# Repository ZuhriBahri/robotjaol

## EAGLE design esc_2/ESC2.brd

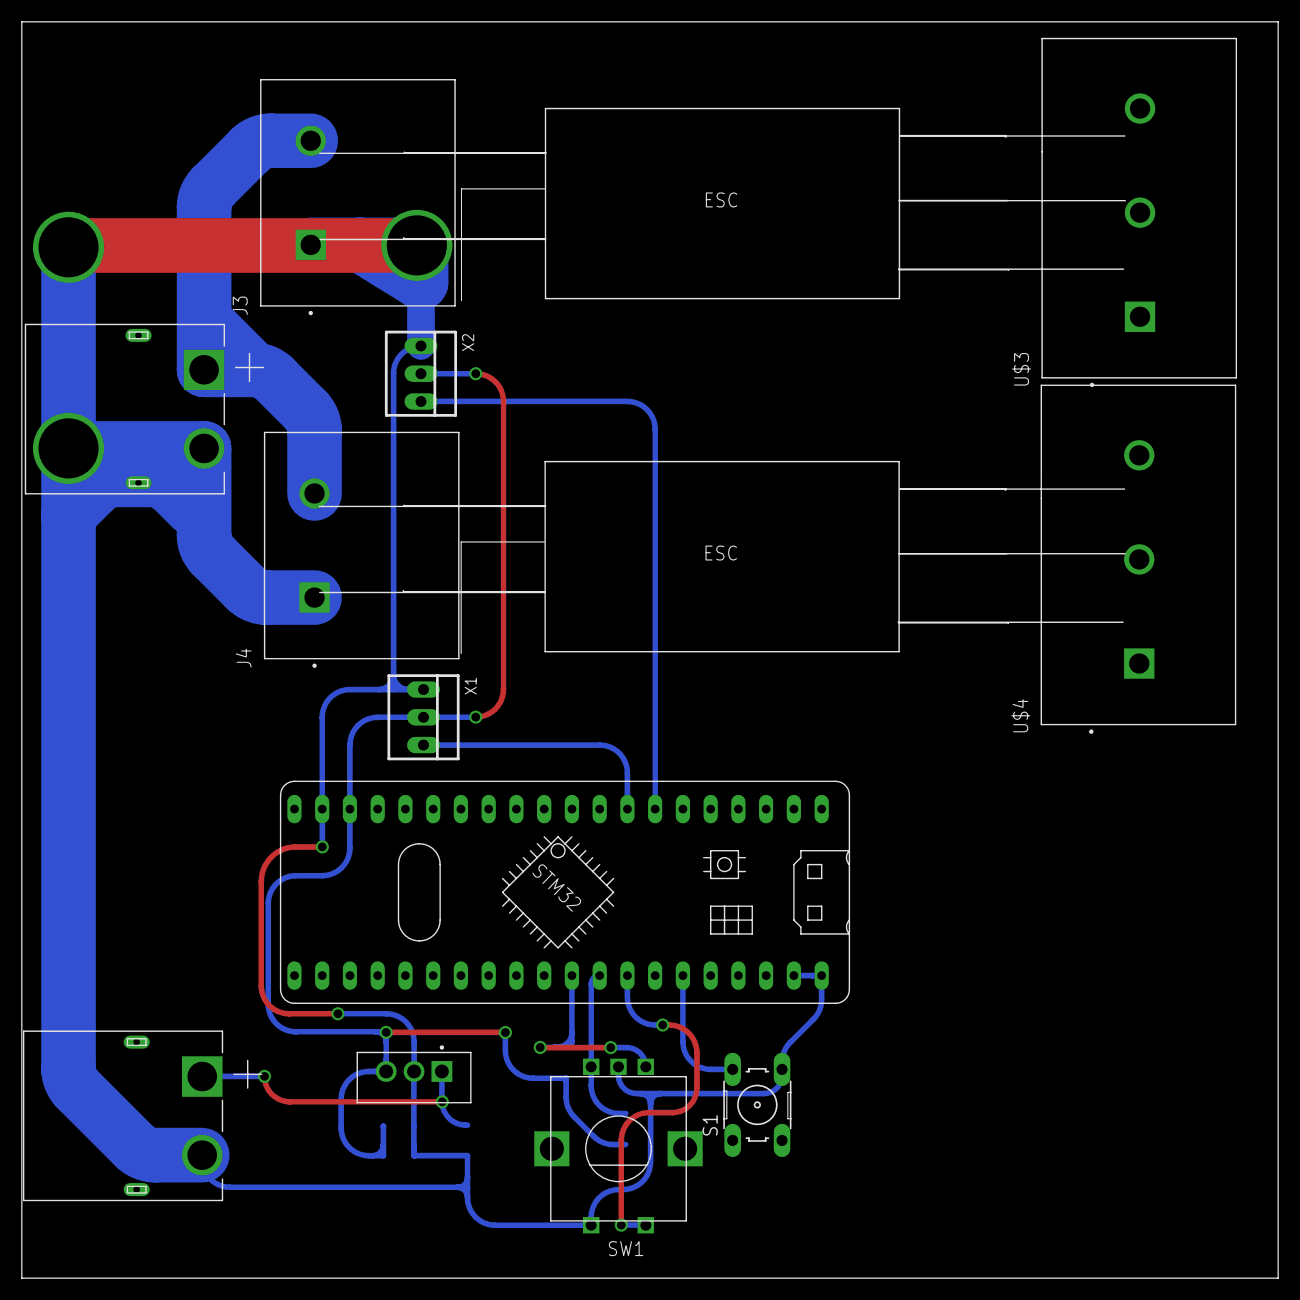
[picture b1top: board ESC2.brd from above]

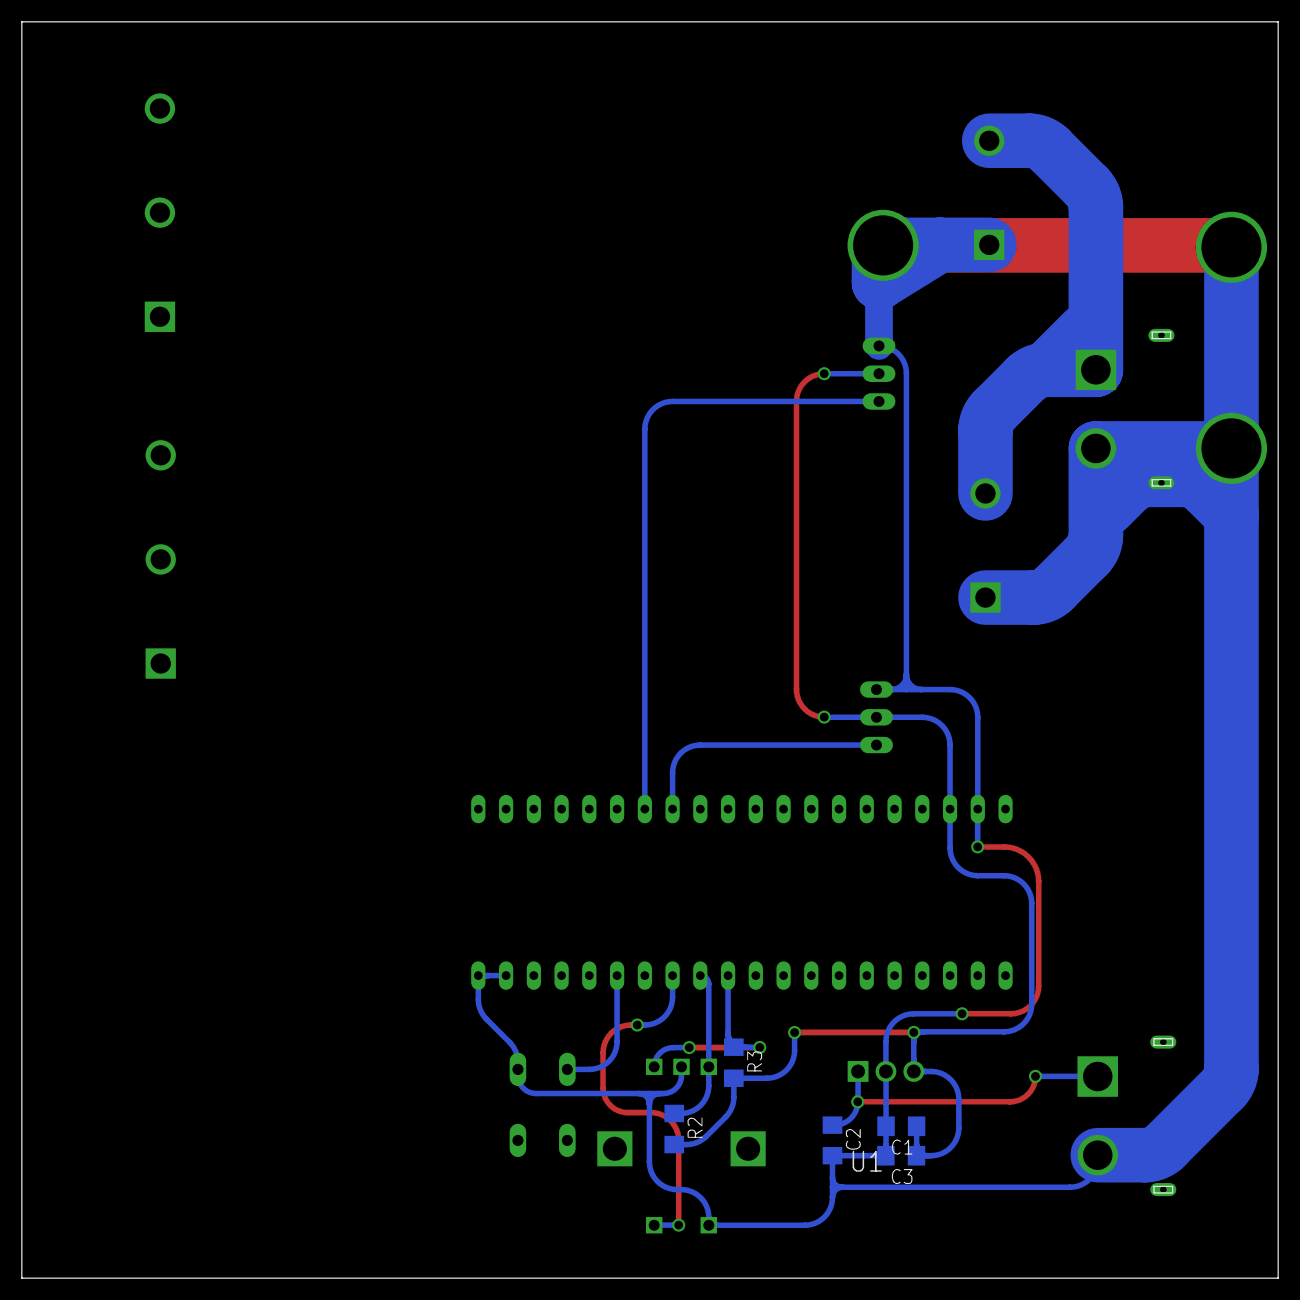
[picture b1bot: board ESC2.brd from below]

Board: 2 copper layers, 115.0 x 115.0 mm, 19 parts (5 on the bottom side), 10 nets.

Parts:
2S: XT60PW-M; AMASS_XT60PW-M
C1, C2, C3: C1206
J3, J4: 4-1437652-6; TE_4-1437652-6
MOD1: BLUE_PILL
R2, R3: R1206
S1: B3F-10XX
SW1: EC12E_SW; ALPS_EC12E_SW
U1: L7805CV; TO255P1040X460X1968-3
U$1, U$2: ESC_LIB; ESC
U$3, U$4: 3-PIN-TB
X1, X2: 22-23-2031
XS: XT60PW-M; AMASS_XT60PW-M

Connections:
2S: 2S.1, C2.1, U1.1
5V: C1.1, C3.1, MOD1.P$18, R2.2, R3.2, U1.3, X1.2, X2.2
BUTTON_RESET_PWM: MOD1.P$26, S1.1, S1.2
ENCODER_CLK&R: MOD1.P$30, R3.1, SW1.A
ENCODER_DT&R: MOD1.P$29, R2.1, SW1.B
ENCODER_RESET: MOD1.P$28, SW1.D
GND: 2S.2, C1.2, C2.2, C3.2, J3.1, J4.1, MOD1.P$19, MOD1.P$21, MOD1.P$22, S1.3, S1.4, SW1.C, SW1.E, U1.2, X1.1, X2.1, XS.2
PWM_MT_1: MOD1.P$8, X1.3
PWM_MT_2: MOD1.P$7, X2.3
XS: J3.2, J4.2, XS.1
